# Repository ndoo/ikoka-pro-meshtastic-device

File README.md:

# Ikoka Pro Meshtastic Device

* Eurocard form factor
  * Half Eurocard - 100 mm × 80mm
  * All I/O in front
* Nordic nrf52840 MCU (EBYTE E73-2G4M08S1C module)
* EBYTE E22 LoRa module (22/30/33 dBm)
* Quectel L76K GPS
* Up to 1.5A solar/DC charging

## PCB Renders

### PCB Top

### PCB Bottom

### Rotating GIF

(Rendered with [kicad-render](https://github.com/linalinn/kicad-render).)

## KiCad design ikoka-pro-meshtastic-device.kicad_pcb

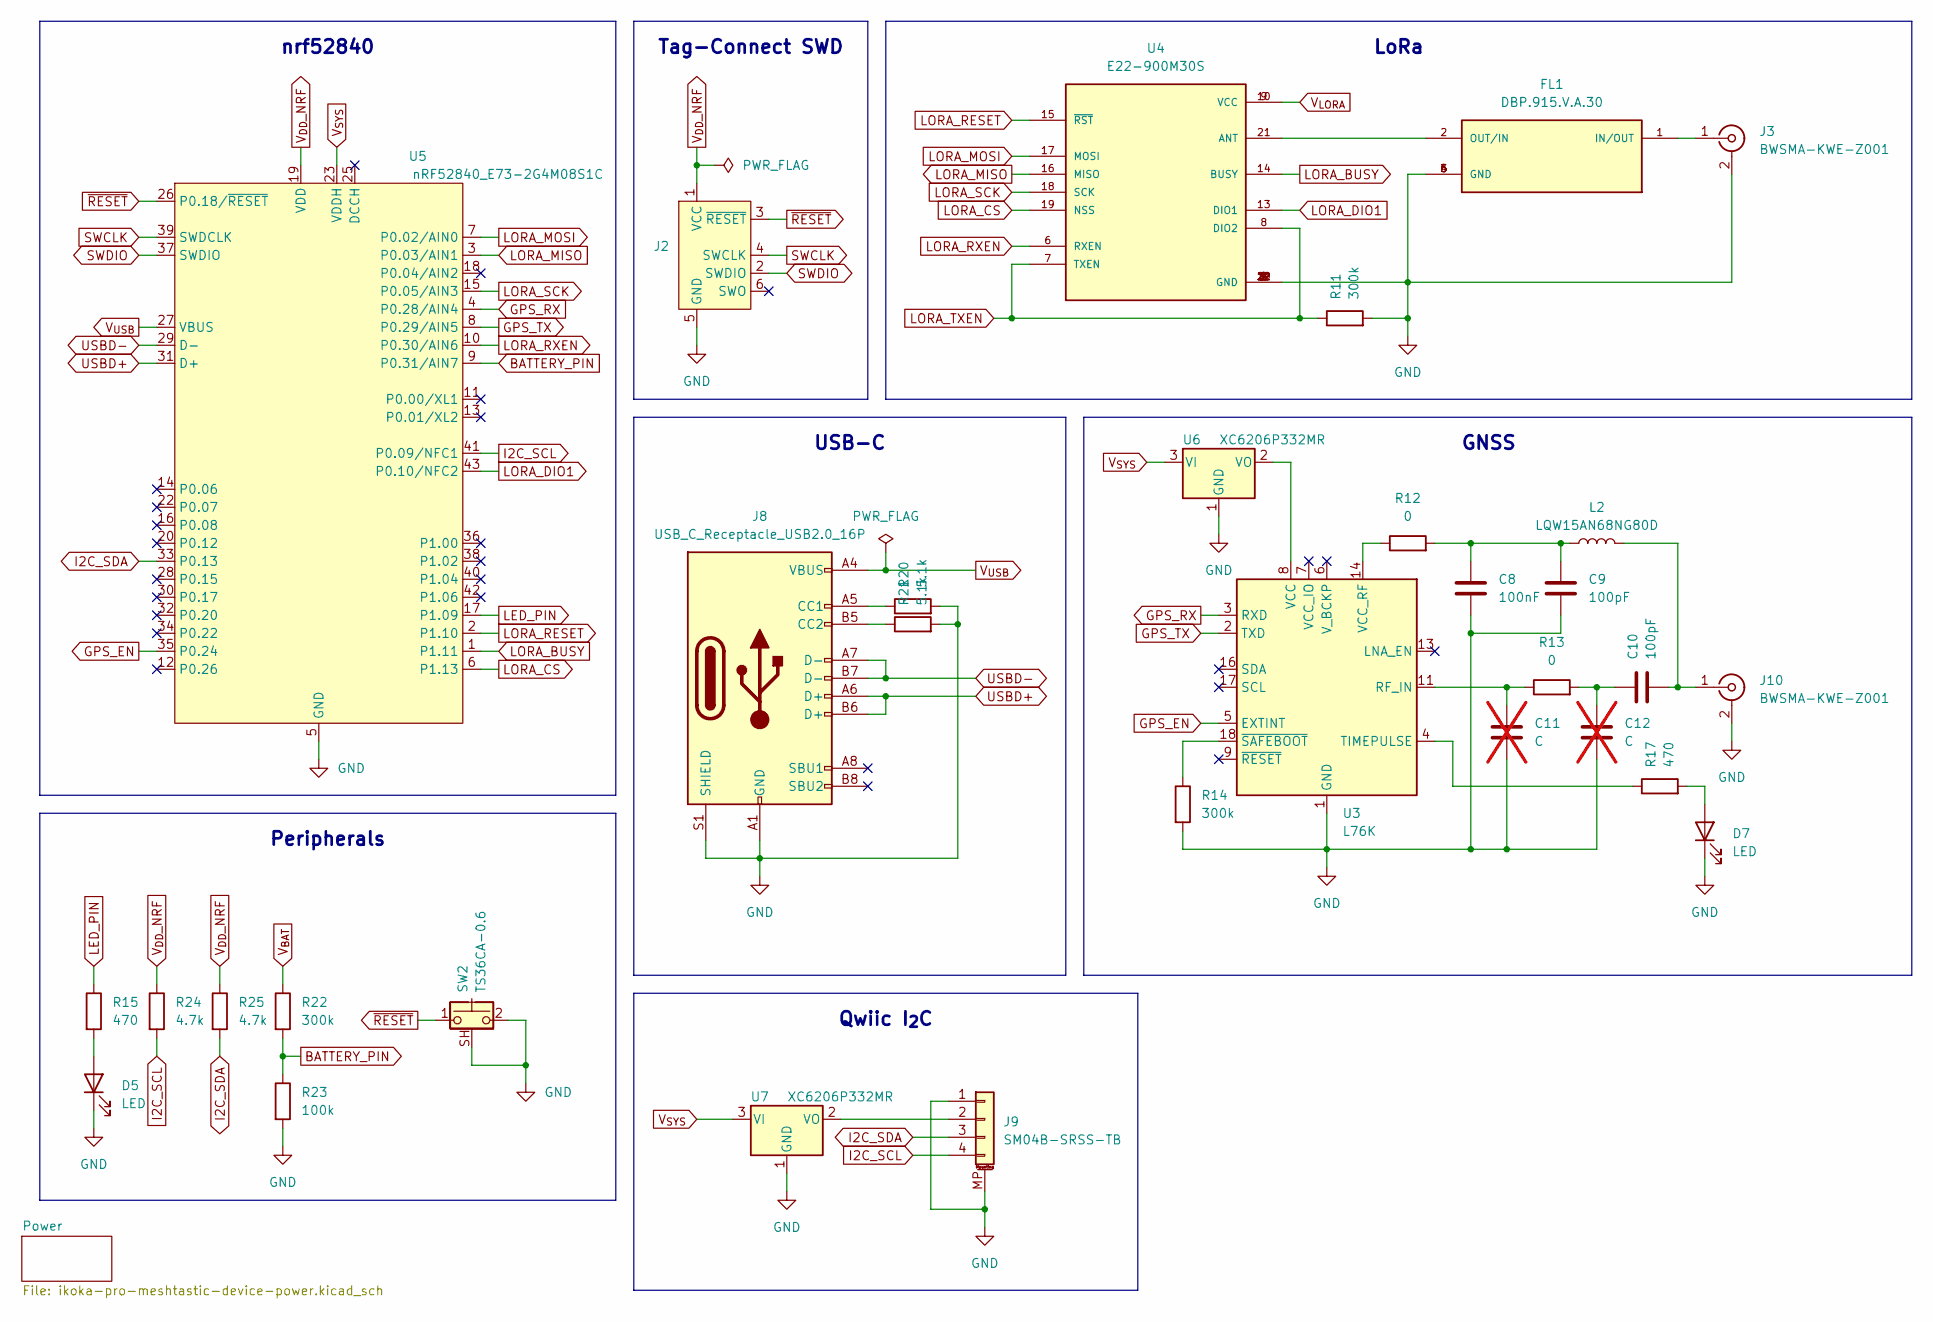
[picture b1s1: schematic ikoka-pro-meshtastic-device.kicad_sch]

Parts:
C8: 100nF; C_0402_1005Metric; MPN CL10A226MQ8NRNC; LCSC C307331
C9, C10: 100pF; C_0402_1005Metric; MPN CL10A226MQ8NRNC; LCSC C1546
C11, C12: C; C_0402_1005Metric; MPN CL10A226MQ8NRNC; LCSC C59461; not fitted
D5, D7: LED; LED_0603_1608Metric; LCSC C2290
FL1: DBP.915.V.A.30; FIL_DBP.915.V.A.30; PARTREV SPE-17-8-060/B/AW; LCSC C3155564
J2: Conn_ARM_JTAG_SWD_10; CON_TC2030_outlined
J3, J10: BWSMA-KWE-Z001; SMA_BAT_Wireless_BWSMA-KWE-Z001; LCSC C496551
J8: USB_C_Receptacle_USB2.0_16P; USB_C_Receptacle_G-Switch_GT-USB-7051x; LCSC C2843970
J9: SM04B-SRSS-TB; JST_SH_SM04B-SRSS-TB_1x04-1MP_P1.00mm_Horizontal; LCSC C160404
L2: LQW15AN68NG80D; L_0402_1005Metric; LCSC C3221844
R11, R14, R22: 300k; R_0402_1005Metric; LCSC C25774
R12, R13: 0; R_0402_1005Metric; LCSC C17168
R15, R17: 470; R_0402_1005Metric; LCSC C25117
R20, R21: 5.1k; R_0402_1005Metric; LCSC C25905
R23: 100k; R_0402_1005Metric; LCSC C25741
R24, R25: 4.7k; R_0402_1005Metric; LCSC C25900
SW2: TS36CA-0.6; SW_SPST_TS36CA-0.6; LCSC C2906288
U3: L76K; ublox_MAX; LCSC C2916234
U4: E22-900M30S; XCVR_E22-900M30S; PARTREV 1.2; LCSC C411294
U5: nRF52840_E73-2G4M08S1C; LCSC C356849
U6, U7: XC6206P332MR; SOT-23-3; LCSC C5446

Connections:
BATTERY_PIN: R22.2, R23.1, U5.9 (P0.31/AIN7)
GND: C8.2, C9.2, C11.2, C12.2, D5.1 (K), D7.1 (K), FL1.3 (GND), FL1.4 (GND), FL1.5 (GND), FL1.6 (GND), J2.5 (GND), J3.2 (Ext), J8.A1 (GND), J8.A12 (GND), J8.B1 (GND), J8.B12 (GND), J8.S1 (SHIELD), J9.1, J9.MP (MountPin), J10.2 (Ext), R11.2, R14.2, R20.2, R21.2, R23.2, SW2.2, SW2.SH (B), U3.1 (GND), U3.10 (GND), U3.12 (GND), U4.1 (GND), U4.2 (GND), U4.3 (GND), U4.4 (GND), U4.5 (GND), U4.11 (GND), U4.12 (GND), U4.20 (GND), U4.22 (GND), U5.5 (GND), U5.21 (GND), U5.24 (GND), U6.1 (GND), U7.1 (GND); also elsewhere on the board
GPS_EN: U3.5 (EXTINT), U5.35 (P0.24)
GPS_RX: U3.3 (RXD), U5.4 (P0.28/AIN4)
GPS_TX: U3.2 (TXD), U5.8 (P0.29/AIN5)
I2C_SCL: J9.4, R24.2, U5.41 (P0.09/NFC1)
I2C_SDA: J9.3, R25.2, U5.33 (P0.13)
LED_PIN: R15.1, U5.17 (P1.09)
LORA_BUSY: U4.14 (BUSY), U5.1 (P1.11)
LORA_CS: U4.19 (NSS), U5.6 (P1.13)
LORA_DIO1: U4.13 (DIO1), U5.43 (P0.10/NFC2)
LORA_MISO: U4.16 (MISO), U5.3 (P0.03/AIN1)
LORA_MOSI: U4.17 (MOSI), U5.7 (P0.02/AIN0)
LORA_RESET: U4.15 (~RST), U5.2 (P1.10); also elsewhere on the board
LORA_RXEN: U4.6 (RXEN), U5.10 (P0.30/AIN6)
LORA_SCK: U4.18 (SCK), U5.15 (P0.05/AIN3)
LORA_TXEN: R11.1, U4.7 (TXEN), U4.8 (DIO2)
unnamed: C8.1, C9.1, L2.1, R12.2
unnamed: C10.1, C12.1, R13.2
unnamed: D5.2 (A), R15.2
unnamed: D7.2 (A), R17.2
unnamed: FL1.1 (IN/OUT), J3.1 (In)
unnamed: FL1.2 (OUT/IN), U4.21 (ANT)
unnamed: J8.A5 (CC1), R20.1
unnamed: J8.B5 (CC2), R21.1
unnamed: J9.2, U7.2 (VO)
unnamed: C10.2, J10.1 (In), L2.2
unnamed: C11.1, R13.1, U3.11 (RF_IN)
unnamed: R17.1, U3.4 (TIMEPULSE)
unnamed: U3.8 (VCC), U6.2 (VO)
unnamed: R12.1, U3.14 (VCC_RF)
unnamed: R14.1, U3.18 (~SAFEBOOT)
SWCLK: J2.4 (SWCLK), U5.39 (SWDCLK)
SWDIO: J2.2 (SWDIO), U5.37 (SWDIO)
USBD+: J8.A6 (D+), J8.B6 (D+), U5.31 (D+)
USBD-: J8.A7 (D-), J8.B7 (D-), U5.29 (D-)
V_{BAT}: R22.1; also elsewhere on the board
V_{DD}_NRF: J2.1 (VCC), R24.1, R25.1, U5.19 (VDD)
V_{LORA}: U4.9 (VCC), U4.10 (VCC); also elsewhere on the board
V_{SYS}: U5.23 (VDDH), U6.3 (VI), U7.3 (VI); also elsewhere on the board
V_{USB}: J8.A4 (VBUS), J8.A9 (VBUS), J8.B4 (VBUS), J8.B9 (VBUS), U5.27 (VBUS)
~RESET: J2.3 (~RESET), SW2.1, U5.26 (P0.18/~RESET)

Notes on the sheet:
LoRa
Peripherals
USB-C
nrf52840
GNSS
Qwiic I_{2}C
Tag-Connect SWD

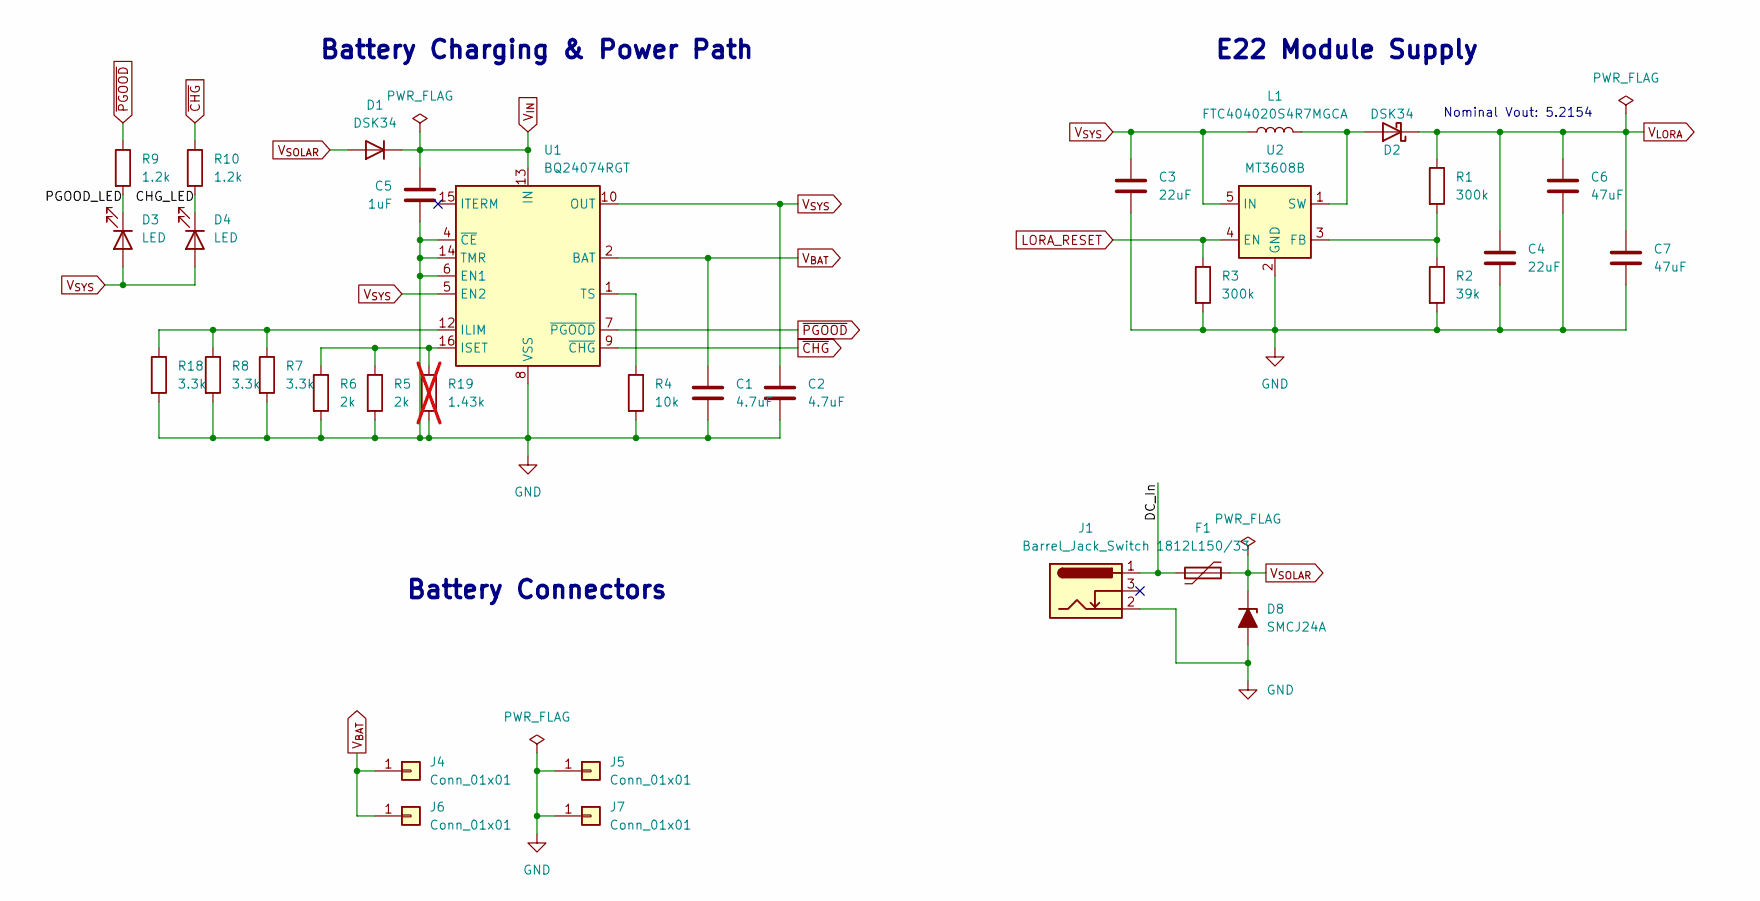
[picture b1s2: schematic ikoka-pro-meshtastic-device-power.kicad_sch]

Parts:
C1, C2: 4.7uF; C_0402_1005Metric; MPN CL10A226MQ8NRNC; LCSC C23733
C3: 22uF; C_0603_1608Metric; LCSC C59461
C4: 22uF; C_0603_1608Metric; MPN CL10A226MQ8NRNC; LCSC C59461
C5: 1uF; C_0402_1005Metric; MPN CL10A226MQ8NRNC; LCSC C52923
C6, C7: 47uF; C_0805_2012Metric; MPN CL10A226MQ8NRNC; LCSC C16780
D1, D2: DSK34; D_SOD-123F; LCSC C7502709
D3, D4: LED; LED_0603_1608Metric; LCSC C2290
D8: SMCJ24A; D_SMC; LCSC C19077604
F1: 1812L150/33; Fuse_1812_4532Metric; LCSC C42369221
J1: Barrel_Jack_Switch; BarrelJack_Horizontal; LCSC C16214
J4, J5, J6, J7: Conn_01x01; BatteryClip_Keystone_54_D16-19mm; LCSC C2685232
L1: FTC404020S4R7MGCA; L_Changjiang_FTC404020S; LCSC C39676072
R1: 300k; R_0402_1005Metric; MPN 0603WAF1502T5E; LCSC C25774
R2: 39k; R_0402_1005Metric; MPN 0603WAF1871T5E; LCSC C25783
R3: 300k; R_0402_1005Metric; LCSC C25774
R4: 10k; R_0402_1005Metric; LCSC C25744
R5, R6: 2k; R_0402_1005Metric; LCSC C4109
R7, R8, R18: 3.3k; R_0402_1005Metric; LCSC C25890
R9, R10: 1.2k; R_0402_1005Metric; LCSC C25862
R19: 1.43k; R_0402_1005Metric; LCSC C25867; not fitted
U1: BQ24074RGT; VQFN-16-1EP_3x3mm_P0.5mm_EP1.6x1.6mm; LCSC C54313
U2: MT3608B; SOT-23-6; LCSC C19189893

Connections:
/Power/CHG_LED: D4.1 (K), R10.2
/Power/DC_In: F1.1, J1.1
/Power/PGOOD_LED: D3.1 (K), R9.2
GND: C1.2, C2.2, C3.2, C4.2, C5.2, C6.2, C7.2, D8.2 (A), J1.2, J5.1, J7.1, R2.2, R3.2, R4.2, R5.2, R6.2, R7.2, R8.2, R18.2, R19.2, U1.4 (~CE), U1.6 (EN1), U1.8 (VSS), U1.14 (TMR), U1.17 (VSS), U2.2 (GND); also elsewhere on the board
LORA_RESET: R3.1, U2.4 (EN); also elsewhere on the board
unnamed: D2.2 (A), L1.1, U2.1 (SW)
unnamed: R7.1, R8.1, R18.1, U1.12 (ILIM)
unnamed: R5.1, R6.1, R19.1, U1.16 (ISET)
unnamed: R4.1, U1.1 (TS)
unnamed: R1.2, R2.1, U2.3 (FB)
V_{BAT}: C1.1, J4.1, J6.1, U1.2 (BAT), U1.3 (BAT); also elsewhere on the board
V_{IN}: C5.1, D1.1 (K), U1.13 (IN)
V_{LORA}: C4.1, C6.1, C7.1, D2.1 (K), R1.1; also elsewhere on the board
V_{SOLAR}: D1.2 (A), D8.1 (K), F1.2
V_{SYS}: C2.1, C3.1, D3.2 (A), D4.2 (A), L1.2, U1.5 (EN2), U1.10 (OUT), U1.11 (OUT), U2.5 (IN); also elsewhere on the board
~CHG: R10.1, U1.9 (~CHG)
~PGOOD: R9.1, U1.7 (~PGOOD)

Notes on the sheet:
E22 Module Supply
Battery Connectors
Battery Charging & Power Path
Nominal Vout: 5.2154

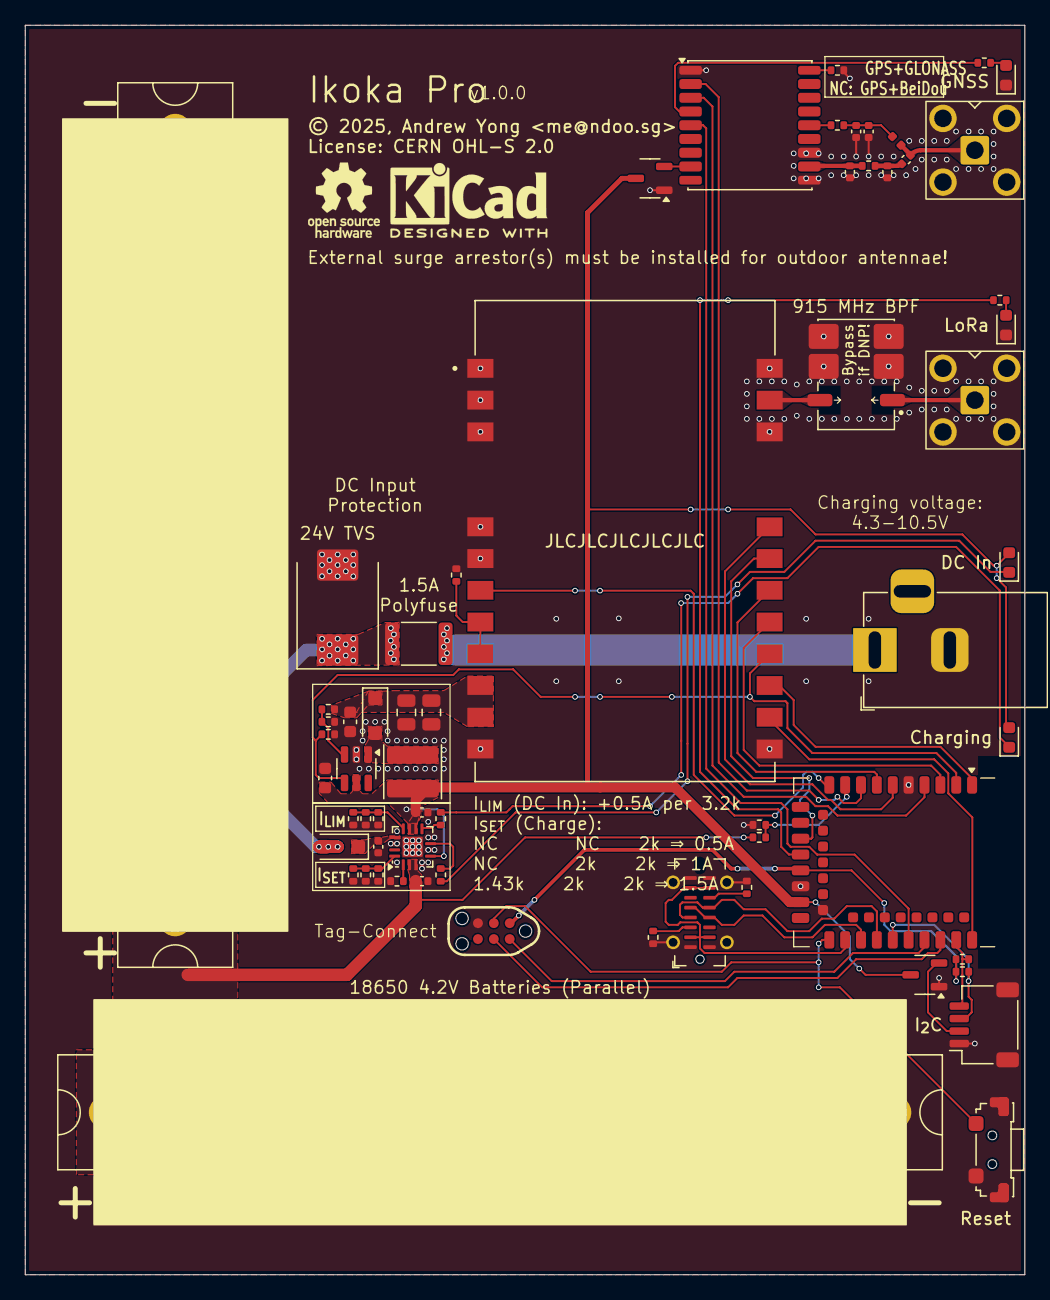
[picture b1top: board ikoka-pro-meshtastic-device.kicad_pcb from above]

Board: 2 copper layers, 80.0 x 100.0 mm, 65 parts (0 on the bottom side), 54 nets.

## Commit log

2025-08-10 docs: Update README.md and add GitHub workflow for PCB images
2025-08-11 feat: Move SWD pads further away from USB-C and battery
2025-08-11 feat(pcbnew): Use R_1812_4532Metric 3dmodel for fuse
2025-08-12 feat: I2C and 100k+300k VBAT divider
    Fixes #1
2025-08-12 chore: v0.9.0 and JLCPCB order placeholder silkscreen
2025-08-12 fix: 4.7kΩ I2C pull-up JLCPCB part selection
2025-08-13 fix: Update TS36CA footprint according to JLCPCB DFM
2025-08-15 fix: Soldermask between pi network on LoRa trace
2025-08-29 fix: Swap GPS Tx and Rx (fixes #5)
2025-08-29 fix(pcbnew): Put soldermask back on RF traces (fixes #6)
2025-08-29 fix(pcbnew): Redraw footprint for Taoglas DBP.915.V.A.30 (fixes #4)
    - Silkscreen re-drawn following KLC guidelines and correctly aligned to part
    - Courtyard re-drawn following KLC guidelines and correctly aligned to part
    - Use 0.25mm roundrects for pads
    - Remove custom soldermask and paste in favor of KiCad pad defaults
2025-08-29 fix: Use correct resistor values for ILIM and default to 1.5A (fixes #7)
2025-08-29 fix: Change USB-C CC resistors from 510Ω to 5.1kΩ (fixes #8)
2025-08-29 chore: v1.0.0 silkscreen

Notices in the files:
ikoka-pro-meshtastic-device.kicad_pcb:
© 2025, Andrew Yong
License: CERN OHL-S 2.0
